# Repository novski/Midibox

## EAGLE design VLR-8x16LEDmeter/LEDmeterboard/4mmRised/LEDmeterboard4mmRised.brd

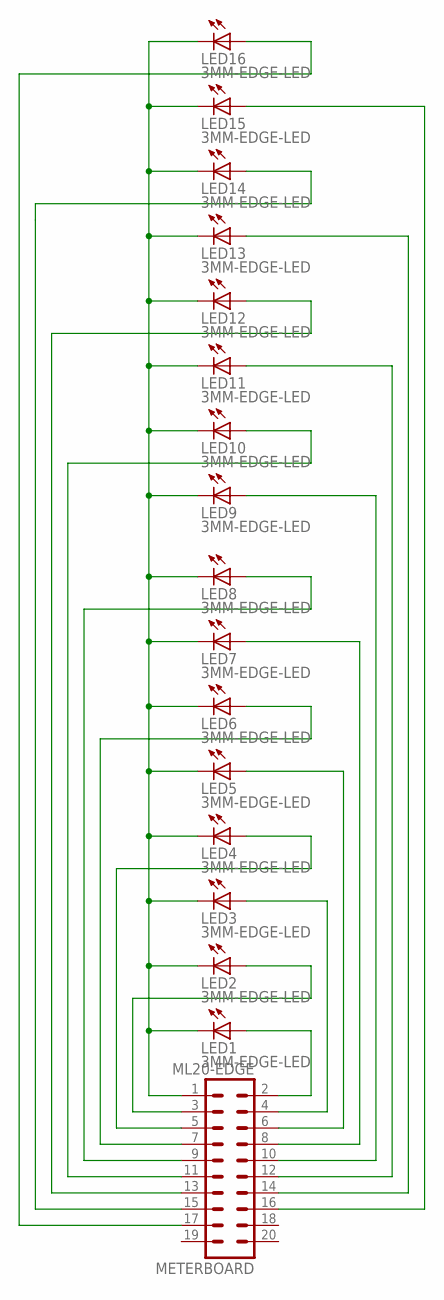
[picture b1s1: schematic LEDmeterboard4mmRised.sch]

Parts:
LED1, LED2, LED3, LED4, LED5, LED6, LED7, LED8, LED9, LED10, LED11, LED12, LED13, LED14, LED15, LED16: 3MM-EDGE-LED
METERBOARD: ML20-EDGE; ML20EDGE

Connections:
unnamed: LED1.KATHODE (C), LED2.KATHODE (C), LED3.KATHODE (C), LED4.KATHODE (C), LED5.KATHODE (C), LED6.KATHODE (C), LED7.KATHODE (C), LED8.KATHODE (C), LED9.KATHODE (C), LED10.KATHODE (C), LED11.KATHODE (C), LED12.KATHODE (C), LED13.KATHODE (C), LED14.KATHODE (C), LED15.KATHODE (C), LED16.KATHODE (C), METERBOARD.1
unnamed: LED1.ANODE (A), METERBOARD.2
unnamed: LED2.ANODE (A), METERBOARD.3
unnamed: LED3.ANODE (A), METERBOARD.4
unnamed: LED4.ANODE (A), METERBOARD.5
unnamed: LED5.ANODE (A), METERBOARD.6
unnamed: LED6.ANODE (A), METERBOARD.7
unnamed: LED7.ANODE (A), METERBOARD.8
unnamed: LED8.ANODE (A), METERBOARD.9
unnamed: LED9.ANODE (A), METERBOARD.10
unnamed: LED10.ANODE (A), METERBOARD.11
unnamed: LED11.ANODE (A), METERBOARD.12
unnamed: LED12.ANODE (A), METERBOARD.13
unnamed: LED13.ANODE (A), METERBOARD.14
unnamed: LED14.ANODE (A), METERBOARD.15
unnamed: LED15.ANODE (A), METERBOARD.16
unnamed: LED16.ANODE (A), METERBOARD.17

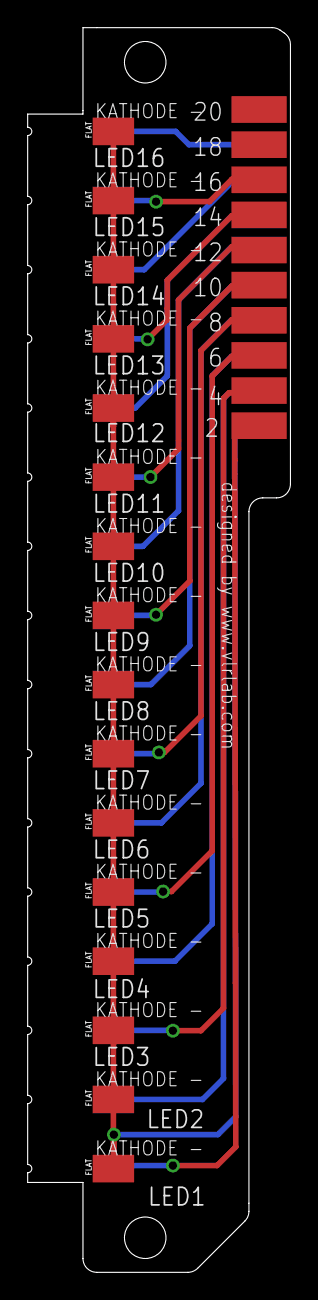
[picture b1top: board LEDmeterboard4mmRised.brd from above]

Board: 2 copper layers, 19.0 x 90.0 mm, 17 parts (1 on the bottom side), 17 nets.

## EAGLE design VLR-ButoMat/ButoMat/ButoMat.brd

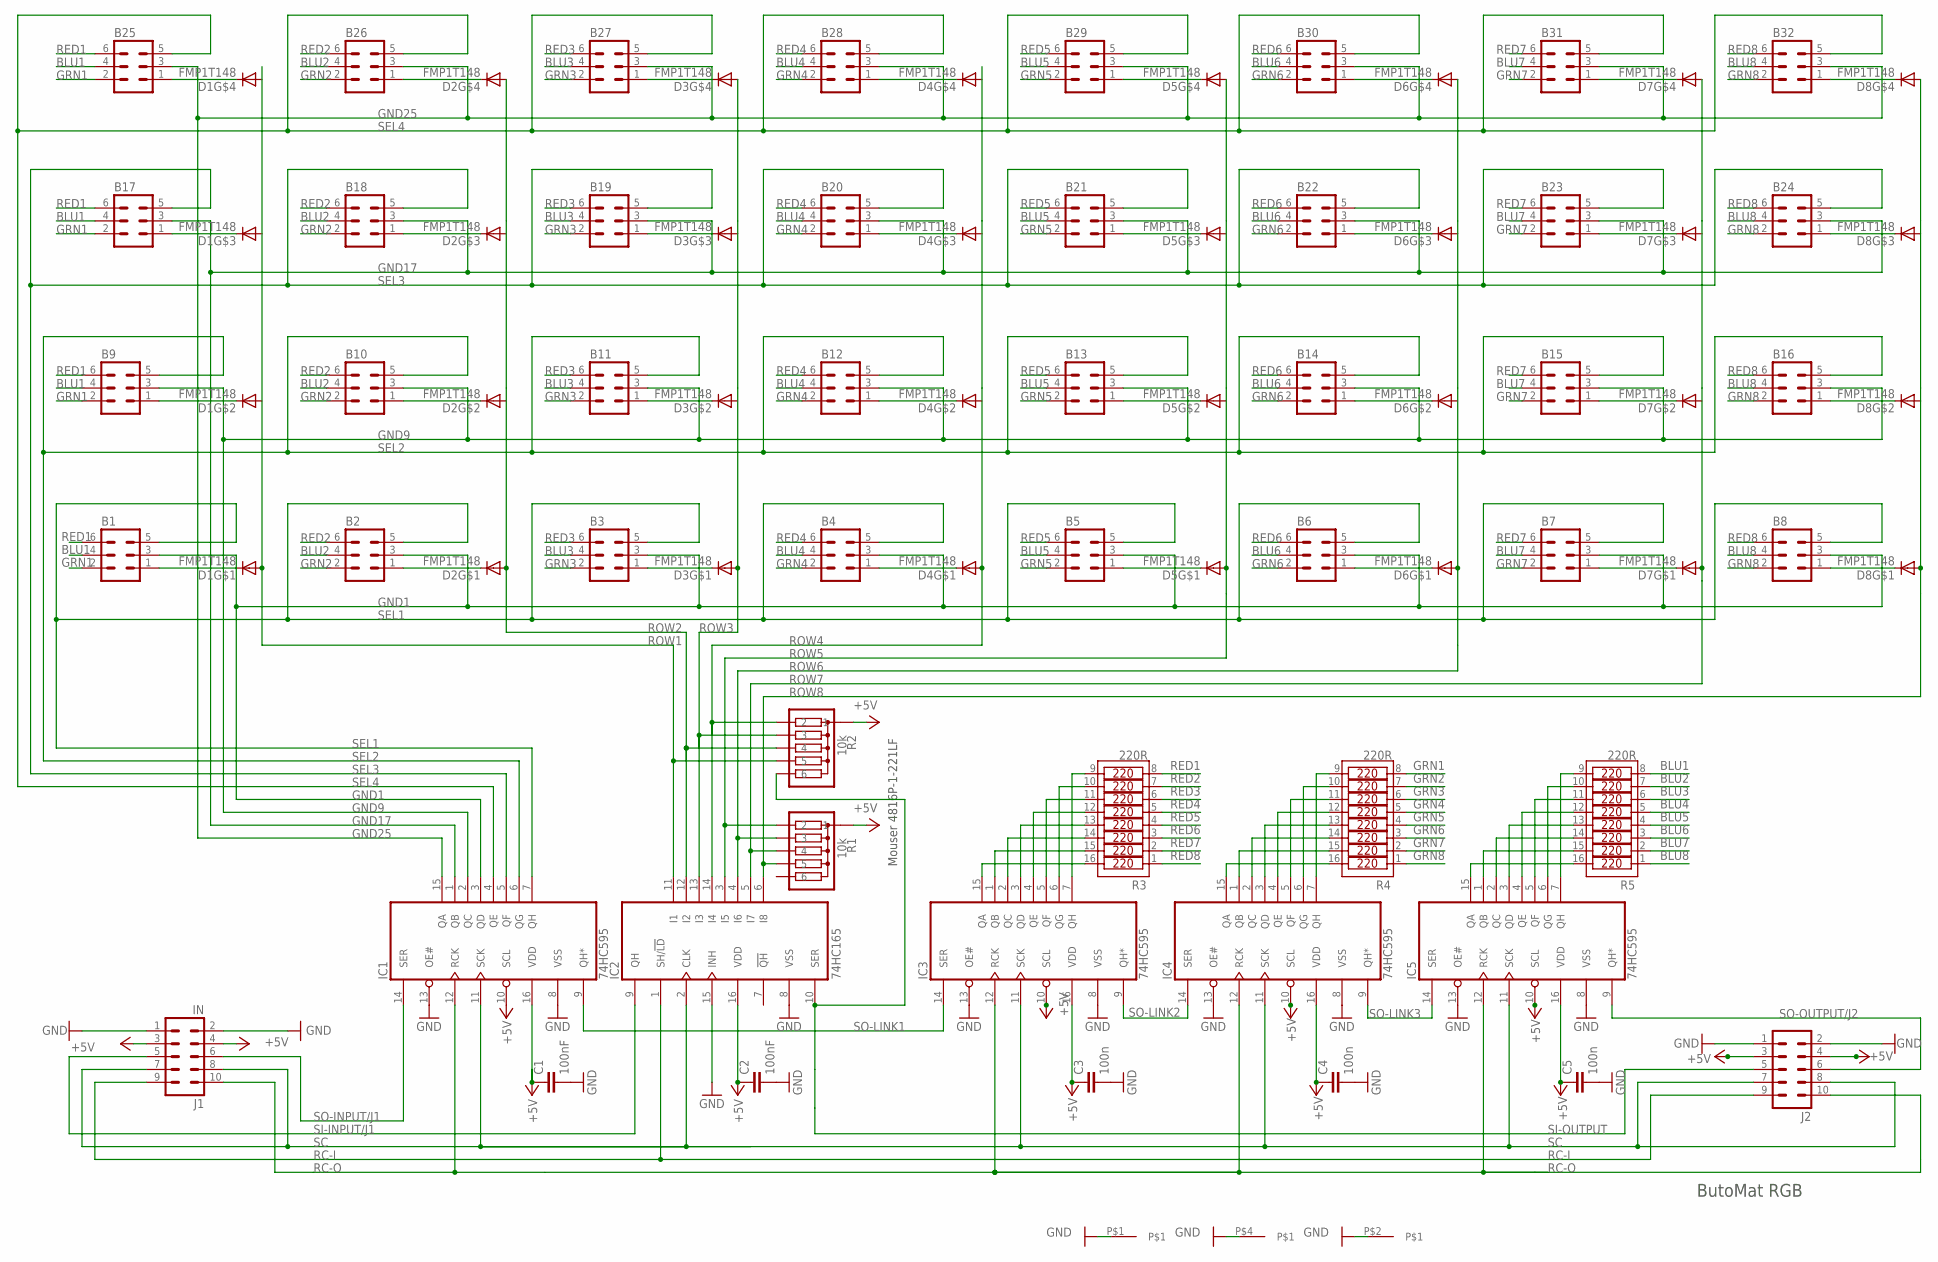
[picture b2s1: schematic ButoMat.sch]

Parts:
B1, B2, B3, B4, B5, B6, B7, B8, B9, B10, B11, B12, B13, B14, B15, B16, B17, B18, B19, B20, B21, B22, B23, B24, B25, B26, B27, B28, B29, B30, B31, B32: ML6
C1, C2: 100nF; C025-030X050
C3, C4, C5: 100n; C025-030X050
D1, D2, D3, D4, D5, D6, D7, D8: FMP1T148; SC-74A
IC1, IC3, IC4, IC5: 74HC595; SO16D
IC2: 74HC165; SO16D
J1: IN; ML10
J2: ML10
R1, R2: 10k; SIL6
R3, R4, R5: 220R; SOIC16W
U$1: MIDIBOX_HALF; MIDIBOX14X6

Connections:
+5V: C1.1, C2.1, C3.1, C4.1, C5.1, IC1.10 (SCL), IC1.16 (VDD), IC2.16 (VDD), IC3.10 (SCL), IC3.16 (VDD), IC4.10 (SCL), IC4.16 (VDD), IC5.10 (SCL), IC5.16 (VDD), J1.3, J1.4, J2.3, J2.4, R1.1, R2.1
BLU1: B1.4, B9.4, B17.4, B25.4, R5.8
BLU2: B2.4, B10.4, B18.4, B26.4, R5.7
BLU3: B3.4, B11.4, B19.4, B27.4, R5.6
BLU4: B4.4, B12.4, B20.4, B28.4, R5.5
BLU5: B5.4, B13.4, B21.4, B29.4, R5.4
BLU6: B6.4, B14.4, B22.4, B30.4, R5.3
BLU7: B7.4, B15.4, B23.4, B31.4, R5.2
BLU8: B8.4, B16.4, B24.4, B32.4, R5.1
GND: C1.2, C2.2, C3.2, C4.2, C5.2, IC1.8 (VSS), IC1.13 (OE#), IC2.8 (VSS), IC2.15 (INH), IC3.8 (VSS), IC3.13 (OE#), IC4.8 (VSS), IC4.13 (OE#), IC5.8 (VSS), IC5.13 (OE#), J1.1, J1.2, J2.1, J2.2, U$1.P$1, U$1.P$2, U$1.P$4
GND1: B1.3, B2.3, B3.3, B4.3, B5.3, B6.3, B7.3, B8.3, IC1.3 (QD)
GND9: B9.3, B10.3, B11.3, B12.3, B13.3, B14.3, B15.3, B16.3, IC1.2 (QC)
GND17: B17.3, B18.3, B19.3, B20.3, B21.3, B22.3, B23.3, B24.3, IC1.1 (QB)
GND25: B25.3, B26.3, B27.3, B28.3, B29.3, B30.3, B31.3, B32.3, IC1.15 (QA)
GRN1: B1.2, B9.2, B17.2, B25.2, R4.8
GRN2: B2.2, B10.2, B18.2, B26.2, R4.7
GRN3: B3.2, B11.2, B19.2, B27.2, R4.6
GRN4: B4.2, B12.2, B20.2, B28.2, R4.5
GRN5: B5.2, B13.2, B21.2, B29.2, R4.4
GRN6: B6.2, B14.2, B22.2, B30.2, R4.3
GRN7: B7.2, B15.2, B23.2, B31.2, R4.2
GRN8: B8.2, B16.2, B24.2, B32.2, R4.1
unnamed: B17.1, D1.K$3 (C)
unnamed: B9.1, D1.K$2 (C)
unnamed: B1.1, D1.K$1 (C)
unnamed: B18.1, D2.K$3 (C)
unnamed: B10.1, D2.K$2 (C)
unnamed: B2.1, D2.K$1 (C)
unnamed: B19.1, D3.K$3 (C)
unnamed: B11.1, D3.K$2 (C)
unnamed: IC5.15 (QA), R5.16
unnamed: IC5.1 (QB), R5.15
unnamed: IC5.2 (QC), R5.14
unnamed: IC5.3 (QD), R5.13
unnamed: IC5.4 (QE), R5.12
unnamed: IC5.5 (QF), R5.11
unnamed: IC5.6 (QG), R5.10
unnamed: IC5.7 (QH), R5.9
unnamed: IC3.15 (QA), R3.16
unnamed: IC3.1 (QB), R3.15
unnamed: IC3.2 (QC), R3.14
unnamed: IC3.3 (QD), R3.13
unnamed: IC3.4 (QE), R3.12
unnamed: IC3.5 (QF), R3.11
unnamed: IC3.6 (QG), R3.10
unnamed: IC3.7 (QH), R3.9
unnamed: B25.1, D1.K$4 (C)
unnamed: B26.1, D2.K$4 (C)
unnamed: B27.1, D3.K$4 (C)
unnamed: B28.1, D4.K$4 (C)
unnamed: B29.1, D5.K$4 (C)
unnamed: B30.1, D6.K$4 (C)
unnamed: B31.1, D7.K$4 (C)
unnamed: B32.1, D8.K$4 (C)
unnamed: IC4.15 (QA), R4.16
unnamed: IC4.1 (QB), R4.15
unnamed: IC4.2 (QC), R4.14
unnamed: IC4.3 (QD), R4.13
unnamed: IC4.4 (QE), R4.12
unnamed: IC4.5 (QF), R4.11
unnamed: IC4.6 (QG), R4.10
unnamed: IC4.7 (QH), R4.9
unnamed: B3.1, D3.K$1 (C)
unnamed: B20.1, D4.K$3 (C)
unnamed: B12.1, D4.K$2 (C)
unnamed: B4.1, D4.K$1 (C)
unnamed: B21.1, D5.K$3 (C)
unnamed: B13.1, D5.K$2 (C)
unnamed: B5.1, D5.K$1 (C)
unnamed: B22.1, D6.K$3 (C)
unnamed: B14.1, D6.K$2 (C)
unnamed: B6.1, D6.K$1 (C)
unnamed: B7.1, D7.K$1 (C)
unnamed: B15.1, D7.K$2 (C)
unnamed: B23.1, D7.K$3 (C)
unnamed: B24.1, D8.K$3 (C)
unnamed: B16.1, D8.K$2 (C)
unnamed: B8.1, D8.K$1 (C)
RC-I: IC2.1 (SH/!LD), J1.9, J2.9
RC-O: IC1.12 (RCK), IC3.12 (RCK), IC4.12 (RCK), IC5.12 (RCK), J1.10, J2.10
RED1: B1.6, B9.6, B17.6, B25.6, R3.8
RED2: B2.6, B10.6, B18.6, B26.6, R3.7
RED3: B3.6, B11.6, B19.6, B27.6, R3.6
RED4: B4.6, B12.6, B20.6, B28.6, R3.5
RED5: B5.6, B13.6, B21.6, B29.6, R3.4
RED6: B6.6, B14.6, B22.6, B30.6, R3.3
RED7: B7.6, B15.6, B23.6, B31.6, R3.2
RED8: B8.6, B16.6, B24.6, B32.6, R3.1
ROW1: D1.ANODE (A), IC2.11 (I1), R2.5
ROW2: D2.ANODE (A), IC2.12 (I2), R2.4
ROW3: D3.ANODE (A), IC2.13 (I3), R2.3
ROW4: D4.ANODE (A), IC2.14 (I4), R2.2
ROW5: D5.ANODE (A), IC2.3 (I5), R1.2
ROW6: D6.ANODE (A), IC2.4 (I6), R1.3
ROW7: D7.ANODE (A), IC2.5 (I7), R1.4
ROW8: D8.ANODE (A), IC2.6 (I8), R1.5
SC: IC1.11 (SCK), IC2.2 (CLK), IC3.11 (SCK), IC4.11 (SCK), IC5.11 (SCK), J1.7, J1.8, J2.7, J2.8
SEL1: B1.5, B2.5, B3.5, B4.5, B5.5, B6.5, B7.5, B8.5, IC1.7 (QH)
SEL2: B9.5, B10.5, B11.5, B12.5, B13.5, B14.5, B15.5, B16.5, IC1.6 (QG)
SEL3: B17.5, B18.5, B19.5, B20.5, B21.5, B22.5, B23.5, B24.5, IC1.5 (QF)
SEL4: B25.5, B26.5, B27.5, B28.5, B29.5, B30.5, B31.5, B32.5, IC1.4 (QE)
SI-INPUT/J1: IC2.9 (QH), J1.5
SI-OUTPUT: IC2.10 (SER), J2.5, R2.6
SO-INPUT/J1: IC1.14 (SER), J1.6
SO-LINK1: IC1.9 (QH*), IC3.14 (SER)
SO-LINK2: IC3.9 (QH*), IC4.14 (SER)
SO-LINK3: IC4.9 (QH*), IC5.14 (SER)
SO-OUTPUT/J2: IC5.9 (QH*), J2.6

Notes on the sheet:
ButoMat RGB
Mouser 4816P-1-221LF

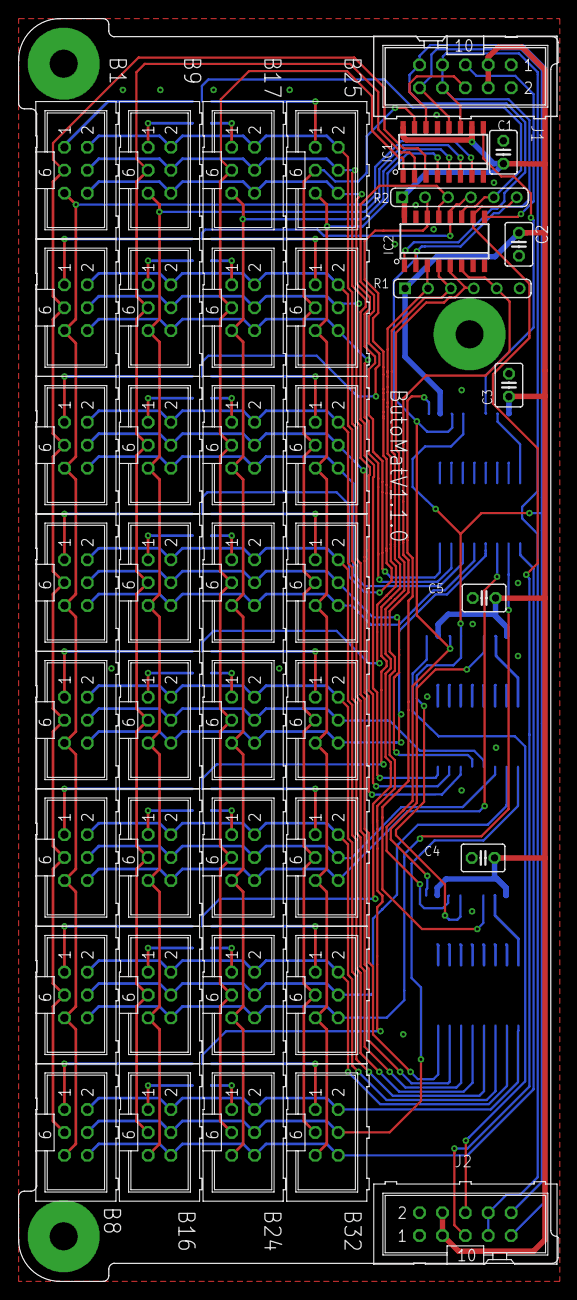
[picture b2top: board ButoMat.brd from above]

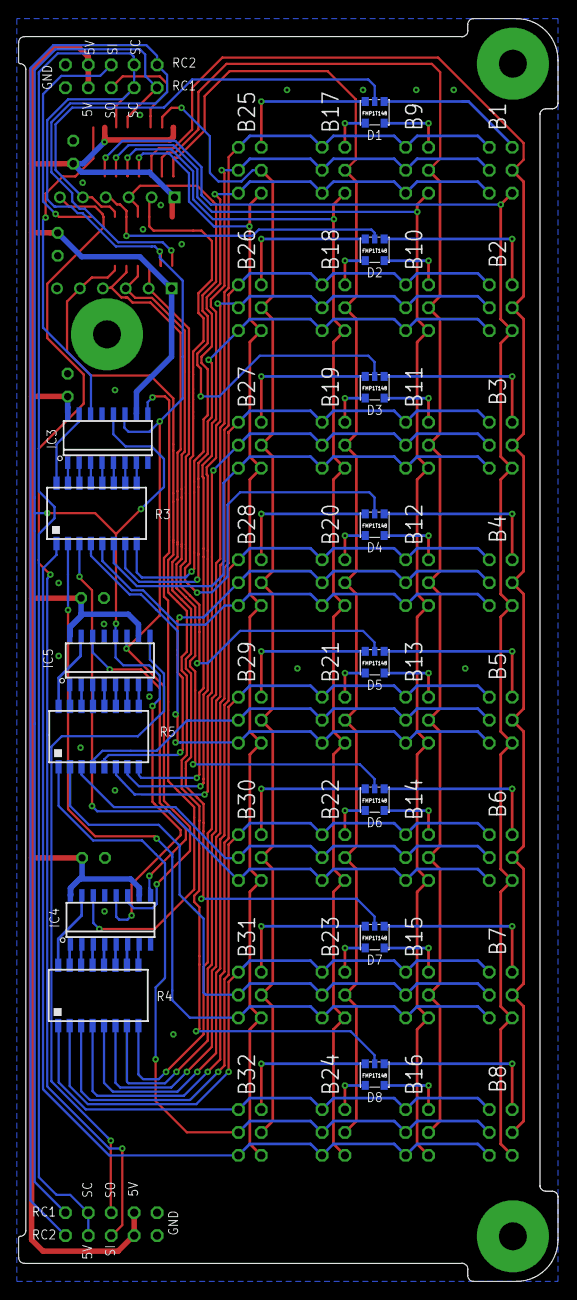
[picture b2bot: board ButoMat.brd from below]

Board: 2 copper layers, 59.8 x 140.0 mm, 59 parts (14 on the bottom side), 108 nets.

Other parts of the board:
U$3: VLRLAB

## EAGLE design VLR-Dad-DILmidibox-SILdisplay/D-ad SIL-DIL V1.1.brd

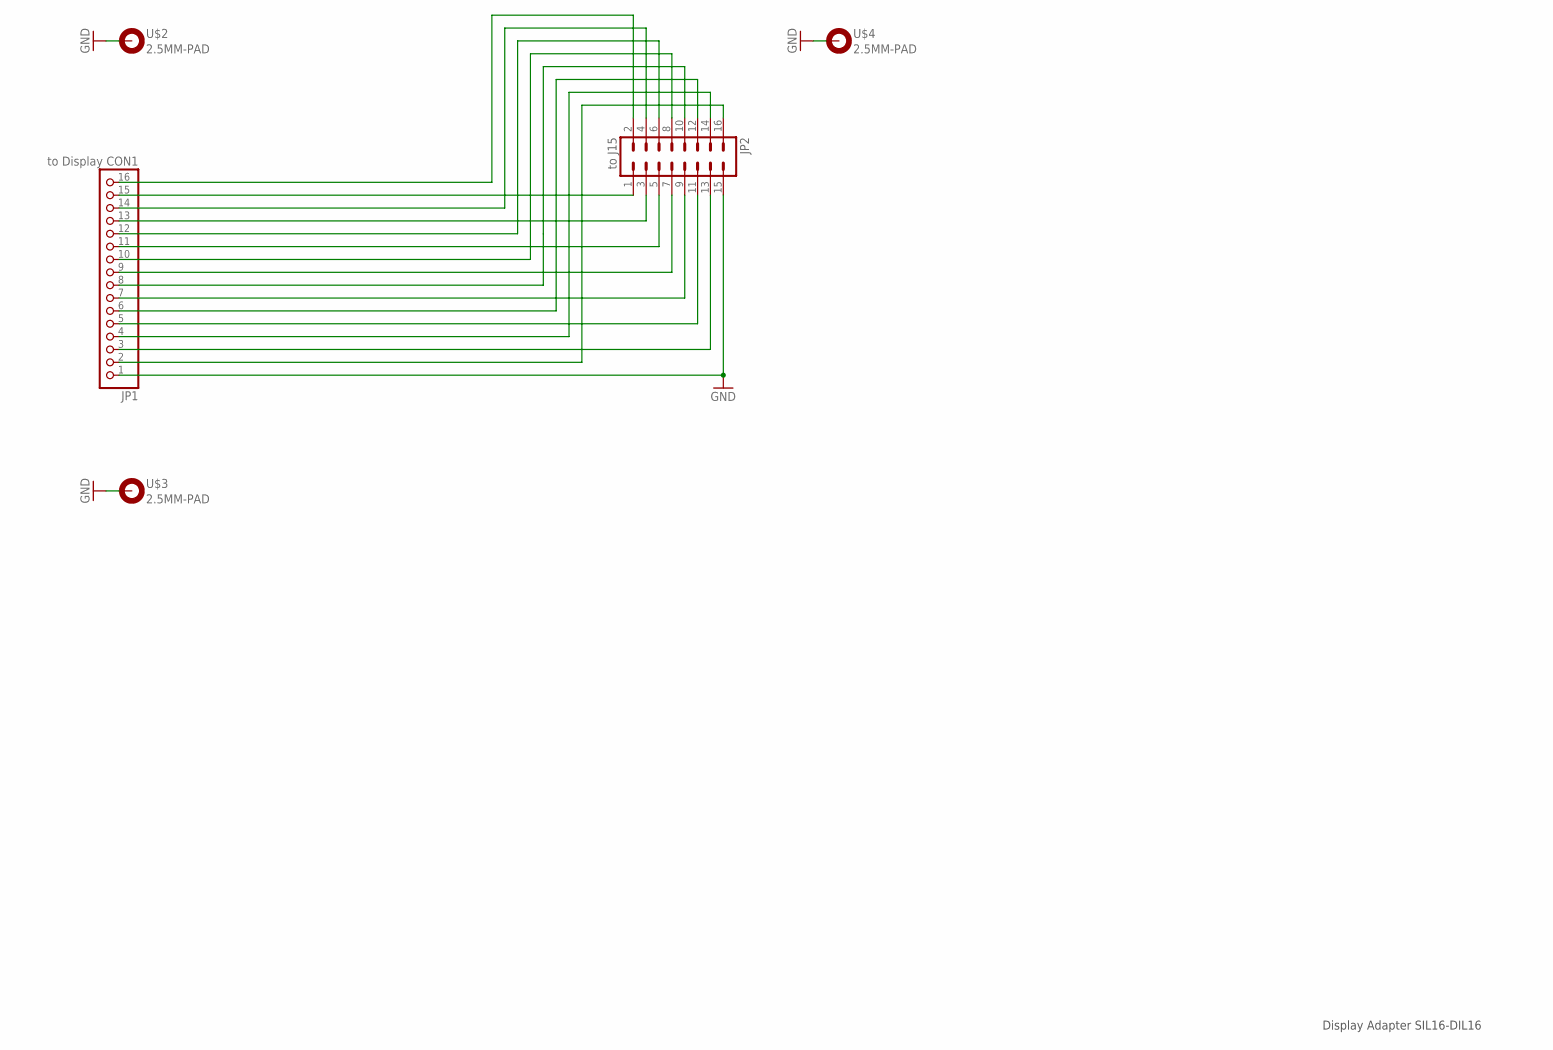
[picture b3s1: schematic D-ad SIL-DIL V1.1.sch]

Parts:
JP1: to Display CON1; 1X16
JP2: to J15; ML16
U$2, U$3, U$4: 2.5MM-PAD

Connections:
DB0: JP1.7, JP2.9
DB1: JP1.8, JP2.10
DB2: JP1.9, JP2.7
DB3: JP1.10, JP2.8
DB4: JP1.11, JP2.5
DB5: JP1.12, JP2.6
DB6: JP1.13, JP2.3
DB7: JP1.14, JP2.4
E: JP1.6, JP2.12
GND: JP1.1, JP2.15, U$2.B3,2, U$3.B3,2, U$4.B3,2
unnamed: JP1.15, JP2.1
N.C: JP1.3, JP2.13
N.C3: JP1.16, JP2.2
R/W: JP1.5, JP2.11
RS: JP1.4, JP2.14
VCC: JP1.2, JP2.16

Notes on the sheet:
Display Adapter SIL16-DIL16

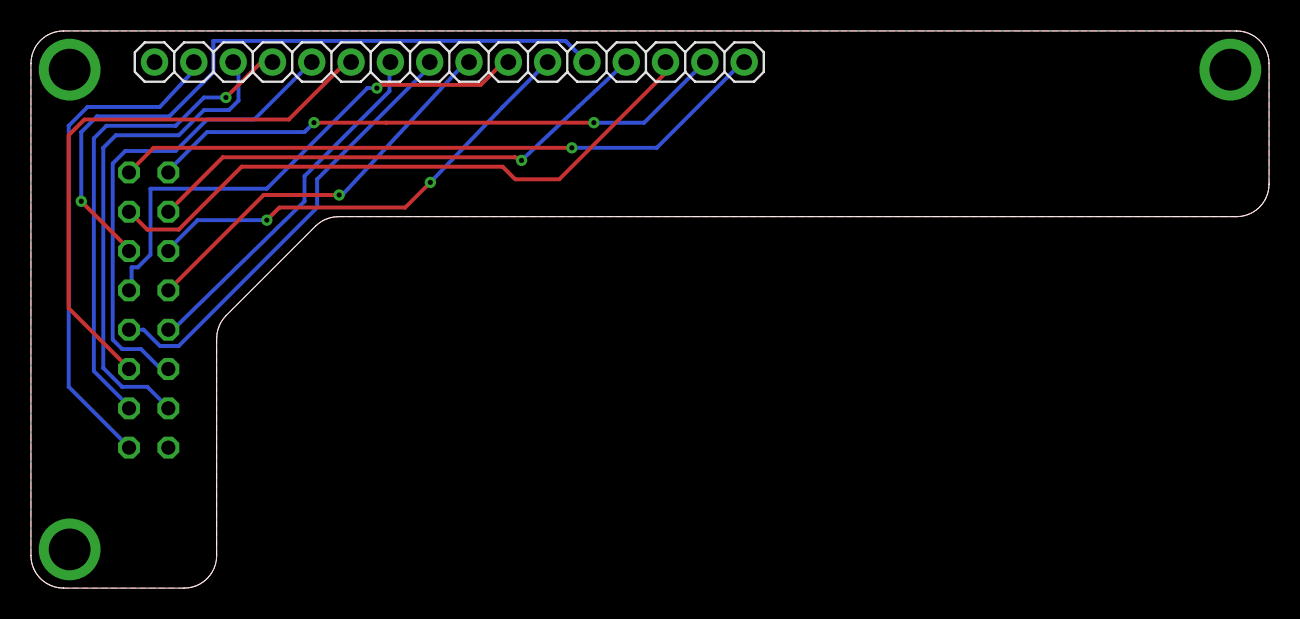
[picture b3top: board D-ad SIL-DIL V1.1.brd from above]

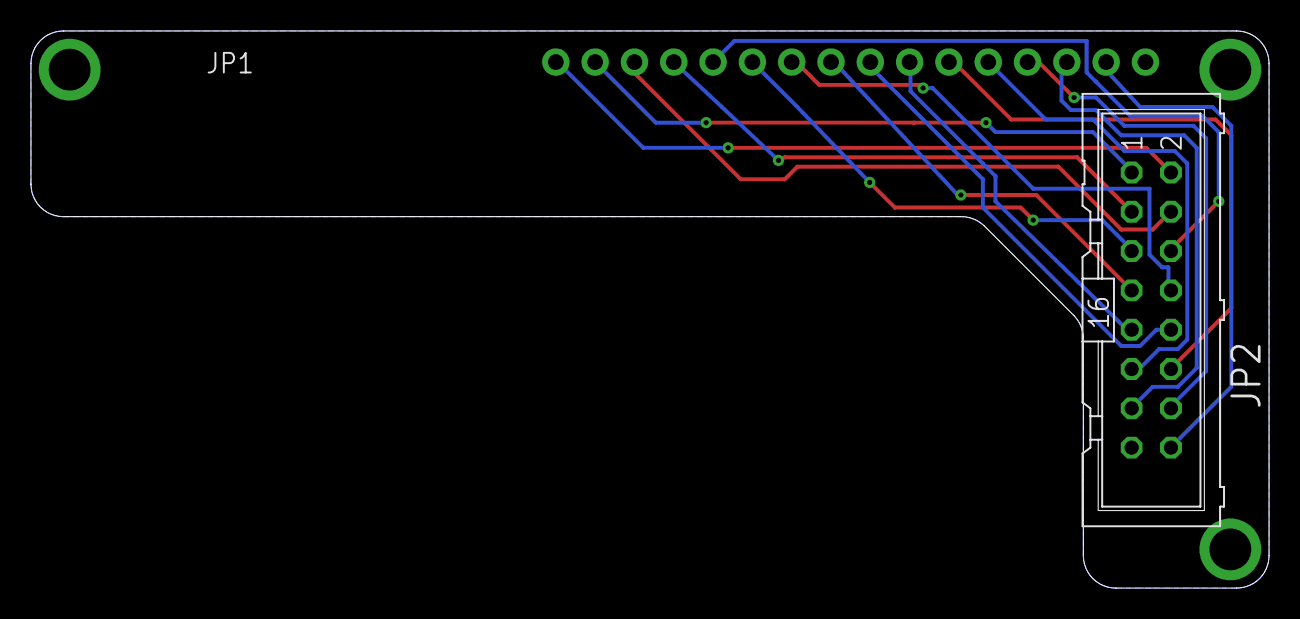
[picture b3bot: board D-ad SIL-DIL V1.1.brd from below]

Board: 2 copper layers, 80.0 x 36.0 mm, 7 parts (3 on the bottom side), 16 nets.

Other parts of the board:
U$5: VLRLAB
U$6: DAD-SILDIL

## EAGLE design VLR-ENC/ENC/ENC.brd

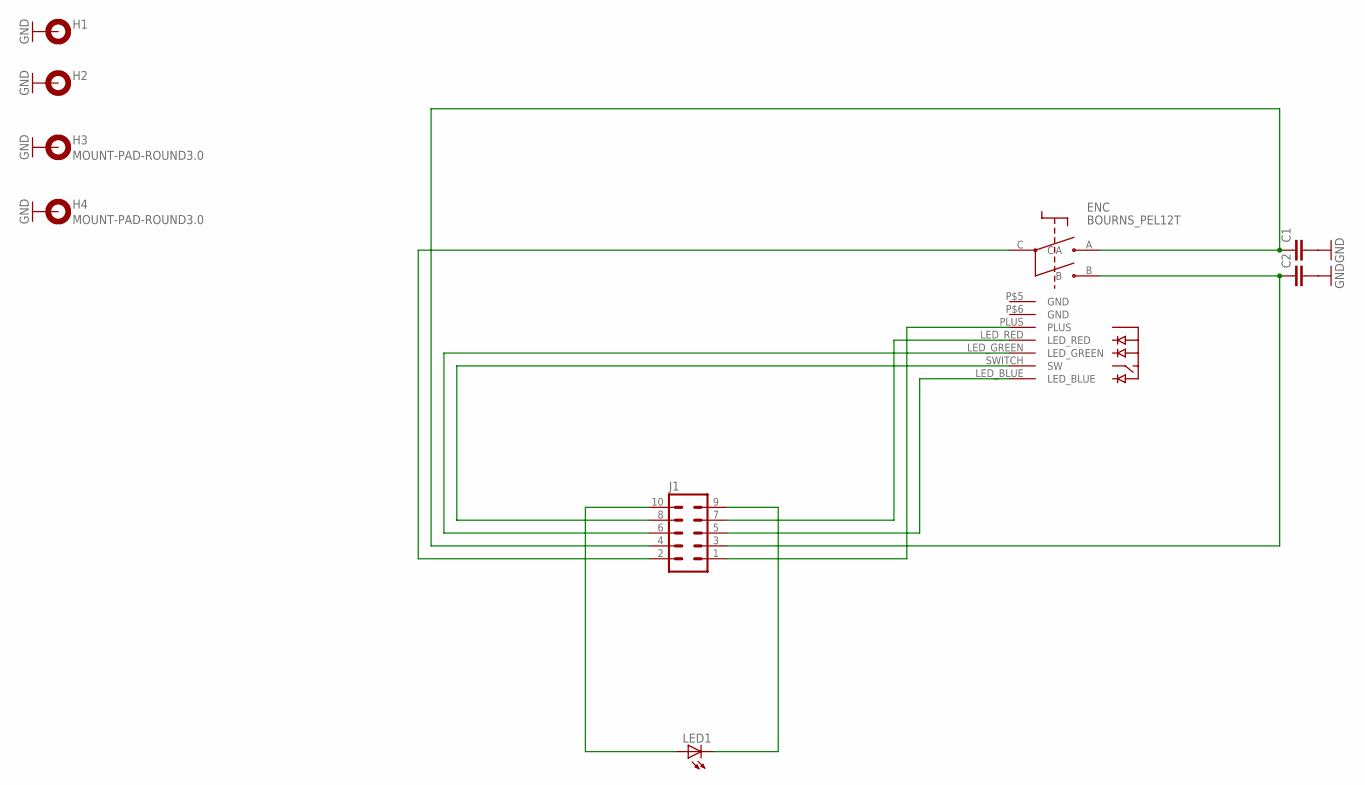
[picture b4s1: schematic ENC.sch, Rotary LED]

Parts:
C1, C2: C-EU025-025X050; C025-025X050
ENC: BOURNS_PEL12T; PEL12T
H1, H2, H3, H4: MOUNT-PAD-ROUND3.0; 3,0-PAD
J1: ML10ML10_TEXTFRONT; ML10_TEXTFRONT
LED1: LED3MM

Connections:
GND: C1.2, C2.2, H1.B3,0, H2.B3,0, H3.B3,0, H4.B3,0
unnamed: ENC.PLUS, J1.1
unnamed: ENC.C, J1.2
unnamed: C2.1, ENC.B, J1.3
unnamed: C1.1, ENC.A, J1.4
unnamed: ENC.LED_BLUE, J1.5
unnamed: ENC.LED_GREEN, J1.6
unnamed: ENC.LED_RED, J1.7
unnamed: ENC.SWITCH (SW), J1.8
unnamed: J1.9, LED1.K (C)
unnamed: J1.10, LED1.A

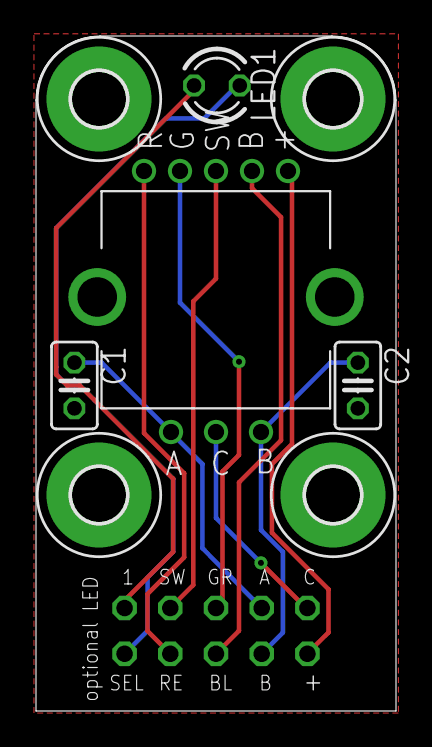
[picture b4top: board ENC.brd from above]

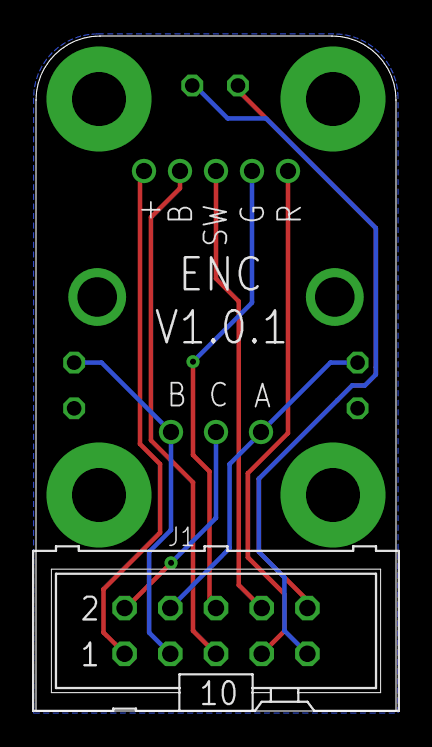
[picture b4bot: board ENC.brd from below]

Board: 2 copper layers, 20.0 x 37.5 mm, 11 parts (2 on the bottom side), 11 nets.

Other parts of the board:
U$1, U$2: VLRLAB_SMAL

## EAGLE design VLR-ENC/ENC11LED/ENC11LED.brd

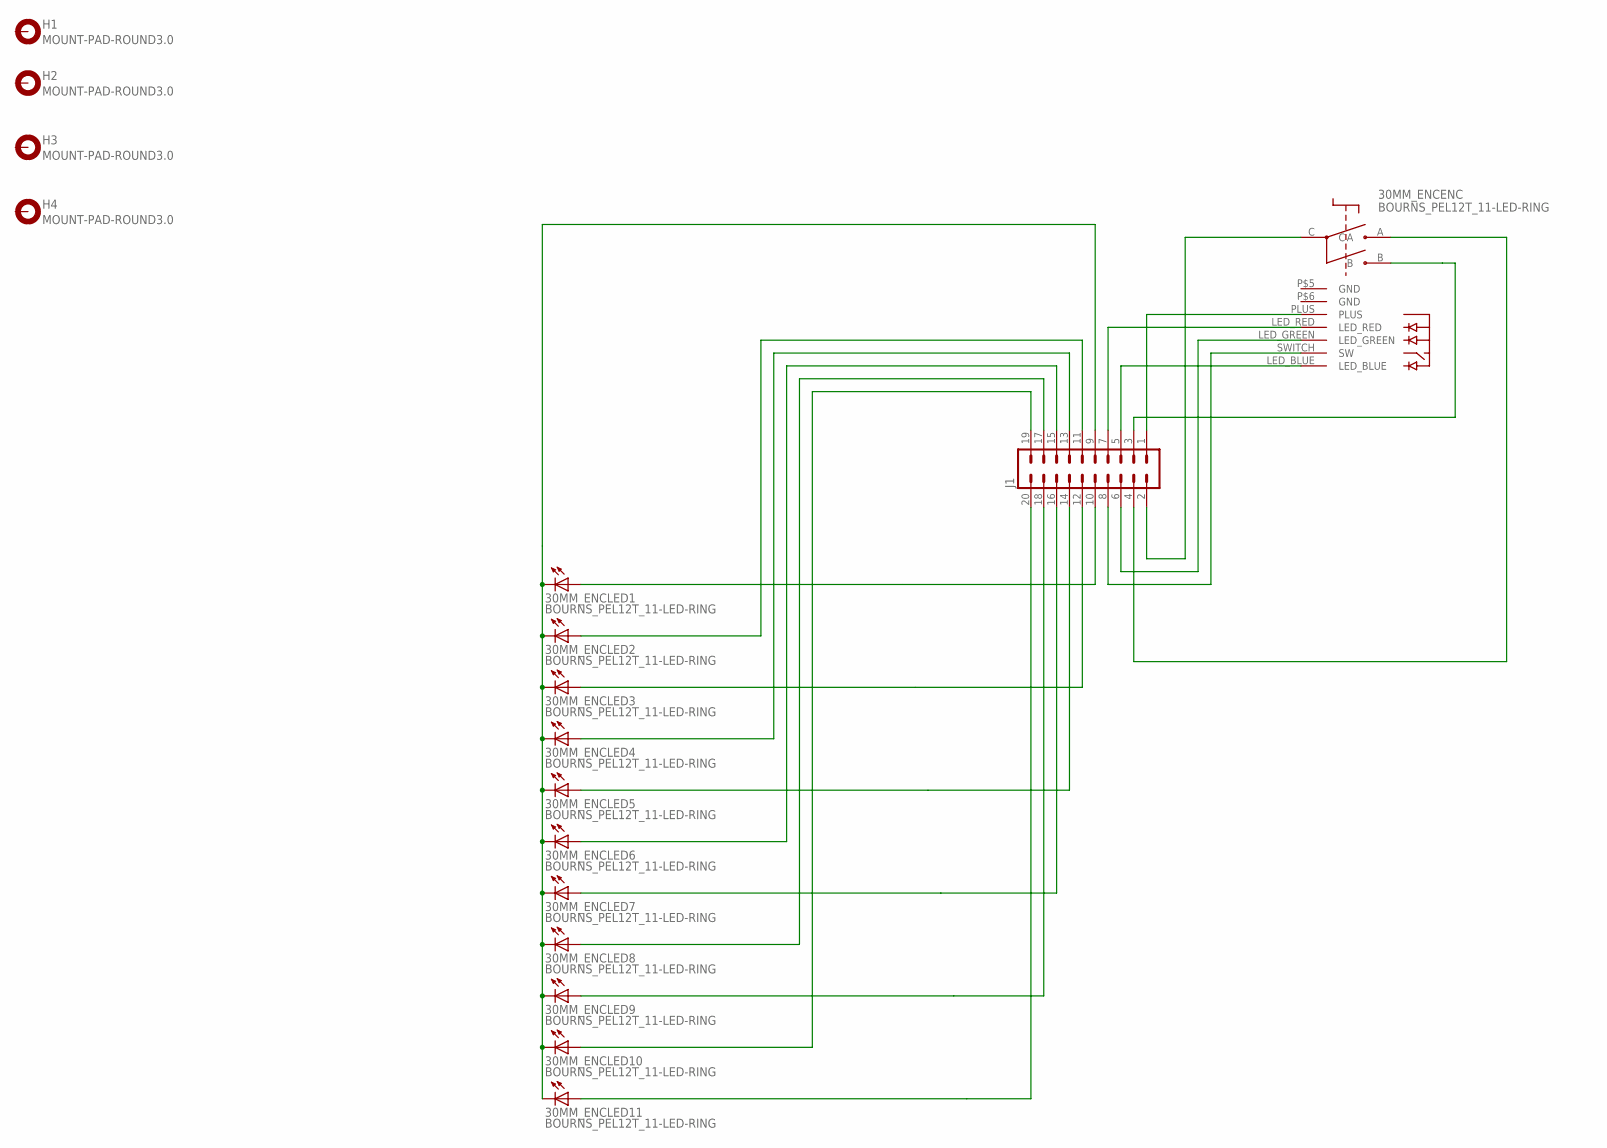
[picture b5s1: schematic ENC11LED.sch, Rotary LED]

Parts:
30MM_ENC: BOURNS_PEL12T_11-LED-RING; PEL12T_11-LED-RING
H1, H2, H3, H4: MOUNT-PAD-ROUND3.0; 3,0-PAD
J1: ML20

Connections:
+: 30MM_ENC.PLUS, J1.1
A: 30MM_ENC.A, J1.4
B: 30MM_ENC.B, J1.3
BLUE: 30MM_ENC.LED_BLUE, J1.5
GREEN: 30MM_ENC.LED_GREEN, J1.6
LED1: 30MM_ENC.A1 (A), J1.10
LED2: 30MM_ENC.A2 (A), J1.11
LED3: 30MM_ENC.A3 (A), J1.12
LED4: 30MM_ENC.A4 (A), J1.13
LED5: 30MM_ENC.A5 (A), J1.14
LED6: 30MM_ENC.A6 (A), J1.15
LED7: 30MM_ENC.A7 (A), J1.16
LED8: 30MM_ENC.A8 (A), J1.17
LED9: 30MM_ENC.A9 (A), J1.18
LED10: 30MM_ENC.A10 (A), J1.19
LED11: 30MM_ENC.A12 (A), J1.20
LED_ROW: 30MM_ENC.K1 (C), 30MM_ENC.K2 (C), 30MM_ENC.K3 (C), 30MM_ENC.K4 (C), 30MM_ENC.K5 (C), 30MM_ENC.K6 (C), 30MM_ENC.K7 (C), 30MM_ENC.K8 (C), 30MM_ENC.K9 (C), 30MM_ENC.K10 (C), 30MM_ENC.K12 (C), J1.9
unnamed: 30MM_ENC.C, J1.2
RED: 30MM_ENC.LED_RED, J1.7
SW: 30MM_ENC.SWITCH (SW), J1.8

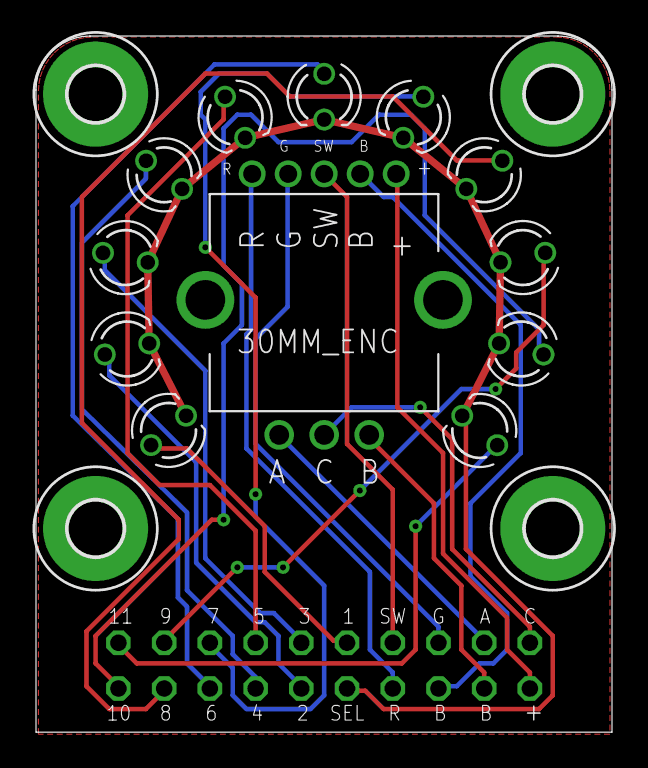
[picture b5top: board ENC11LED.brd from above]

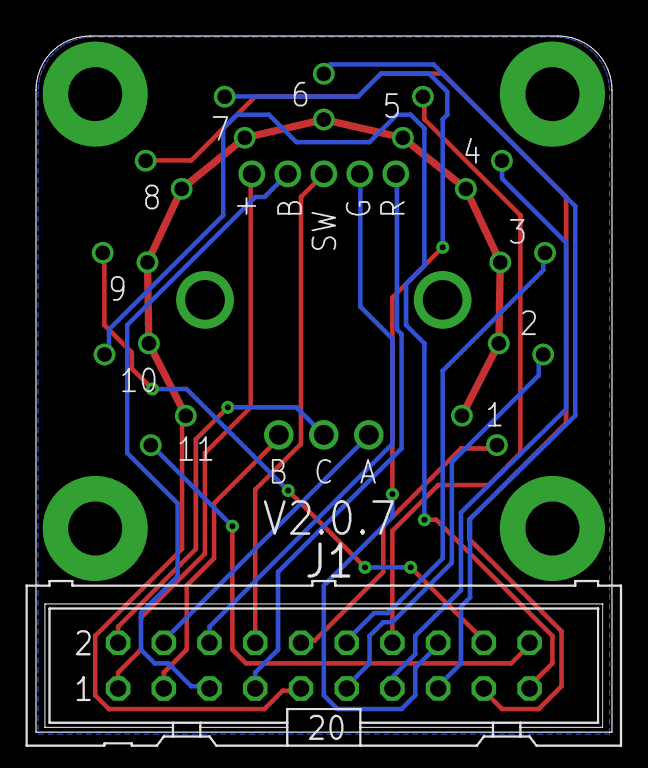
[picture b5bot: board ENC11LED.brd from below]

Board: 2 copper layers, 32.0 x 38.7 mm, 8 parts (2 on the bottom side), 20 nets.

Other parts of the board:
U$1, U$2: VLRLAB_SMAL
